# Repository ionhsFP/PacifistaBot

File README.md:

# PacifistaBot: Kit Humanoide de iniciación

Este Kit está pensado para todo aquel que quiera iniciarse en la competición de humanoides. Está diseñado con piezas estandarizadas, baratas, fácil de conseguir y pensado para ser de fácil montaje y programación. Está creado en su totalidad a base de impresión 3D, se programa desde un Arduino Nano y usa una placa controladora fácil de soldar.

Hay que destacar que el robot ha sido diseñado por OPRobots y han liberado las fuentes para que cualquiera pueda replicarlo, modificarlo o seguir desarrollándolo. Aunque su diseño inicial esté inspirado en los robots Pacifistas de la serie One Piece, el diseño es totalmente personalizable ya que tanto las manos y la cabeza, como los detalles decorativos de su pecho y piernas son totalmente modificables e intercambiables para conseguir un robot único.

Mediante este Kit se puede profundizar diferentes niveles de competencias técnicas, de las siguientes áreas STEM:

- Electrónica
- Mecatrónica
- Programación
- Dibujo
- Impresión 3D

El robot pacifistabot originalmente se ha diseñado para controlado por bluetooth. Partiendo de la idea original se ha modificado creando una nueva versión en la que se puede elegir controlarlo mediante bluetooth o mediante wifi (los 2 a la vez no se puede). En la siguiente tabla se puede ver la documentación de cada versión de robot.

| Pacifistabot                                              | Pacifistabot-ESP                                           | Pacifistabot-AlhII                                        |
| --------------------------------------------------------- | ---------------------------------------------------------- | --------------------------------------------------------- |
| [Material y Equipos](./montaje/MATERIAL-EQUIPOS.md)       | [Material y Equipos](./montaje/MATERIAL-EQUIPOS-ESPyBT.md) | [Material y Equipos](./montaje/MATERIAL-EQUIPOS-AlhII.md) |
| [Montaje y Calibración](./montaje/MONTAJE-CALIBRACION.md) | Montaje y Calibración                                      | Montaje y Calibración                                     |

El coste del material de montaje es inferior a 100 euros y para facilitar poder empezar a montar se ha documentado un listado de Material y Equipos necesarios. Clasificándolos por piezas 3D, componentes mecánicos, componentes electrónicos y equipos de trajo y herramientas.

Para guiar en el proceso de creación de robot, se ha documentado el proceso de Montaje y Calibración. En él se encuentra el proceso de montaje-ajustes mecánicos, montaje electrónico y calibración del robot.

Las especificaciones principales son:

DIMENSIONES

------

- Producto contraido: 320 x 220 x 160 mm
- Producto extendido: 450 x 600 x110 mm

PESO

------

- Producto: 1000 g ~

MATERIALES

------

- Piezas impresas en PLA o ABS
- Tornillos de acero inox.

COMPONENTES ELECTRÓNICOS

------

- 12 Servomotores MG 996R
- Bateria LiFe 6,6V 1100	mAh
- Controladora Arduino Nano
- Módulo Bluetooth hc-05
- Módulo Wifi ESP-01 (solo en Versión Pacifistabot-ESP)

COMUNICACIÓN

------

- Cable mini-Usb
- Bluetooth
- Wifi (solo en Versión Pacifistabot-ESP)
- Programación mediante OTA (Over The Air)(solo en Versión Pacifistabot-ESP)

SOFTWARE

------

- Programación: [Arduino IDE](https://www.arduino.cc/)
- Diseño electrónico: [Kicad](https://www.kicad-pcb.org/)
- Diseño mecánico: [Skeetup](https://www.sketchup.com/)
- Comunicacción: [Putty](https://www.putty.org) / [Arduino IDE](https://www.arduino.cc/) / [ScriptCommunicator](https://github.com/szieke/ScriptCommunicator_serial-terminal) /...
- APP android: [Bluetooth Electronics](https://www.keuwl.com/apps/bluetoothelectronics/) / [BlueTerm](https://play.google.com/store/apps/details?id=es.pymasde.blueterm&hl=en_US) / ...

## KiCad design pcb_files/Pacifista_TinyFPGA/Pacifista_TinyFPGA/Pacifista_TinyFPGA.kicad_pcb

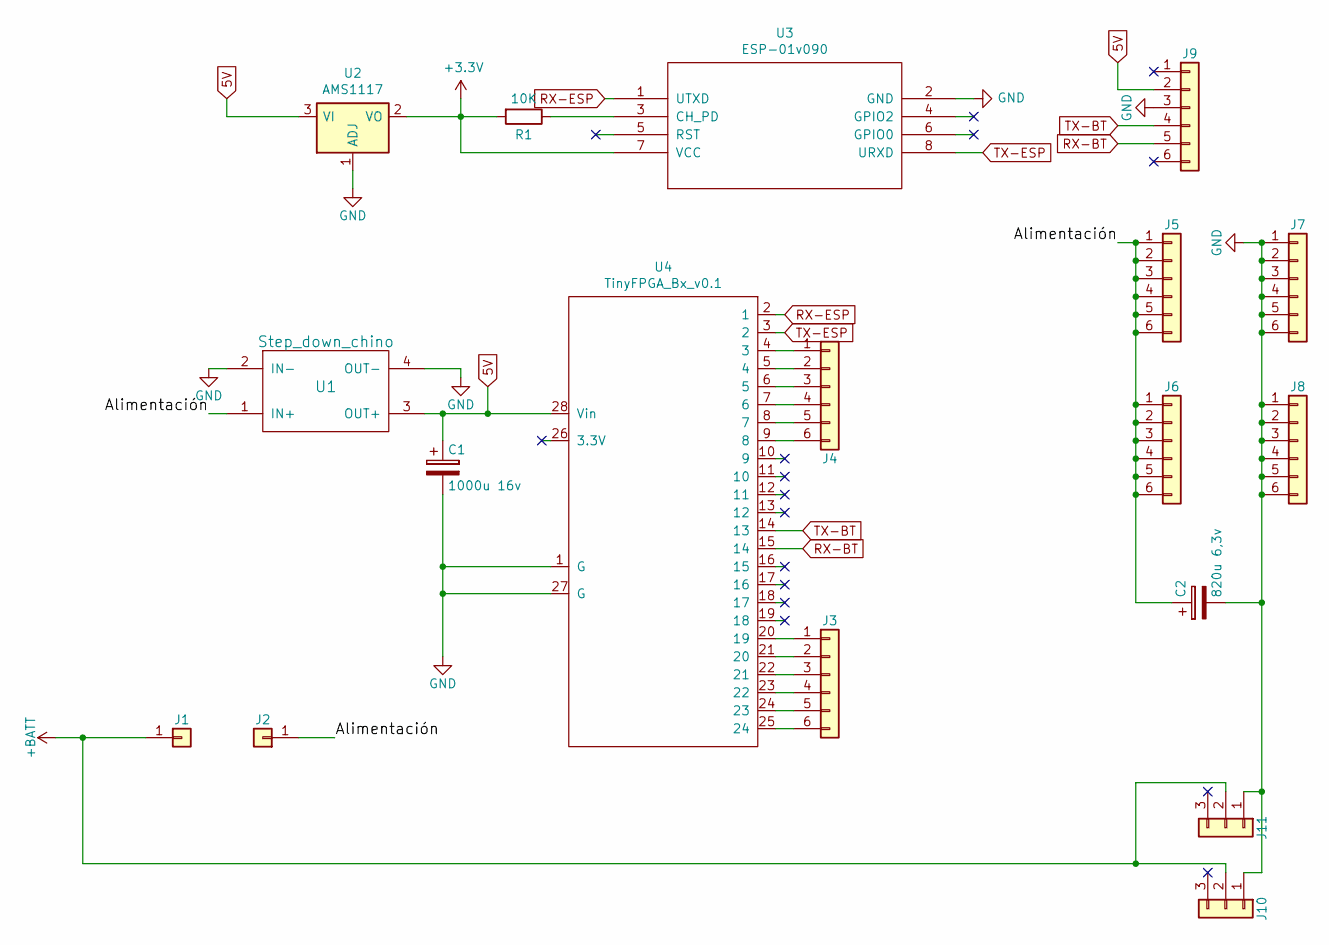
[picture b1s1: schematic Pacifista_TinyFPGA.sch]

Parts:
C1: 1000u 16v; CP_Radial_D8.0mm_P3.80mm
C2: 820u 6,3v; CP_Radial_D10.0mm_P5.00mm
J1, J2: Conn_01x01; SolderWirePad_single_1-5mmDrill
J3: Conn_01x06; PinSocket_1x06_P2.54mm_Vertical
J4, J5, J6, J7, J8: Conn_01x06; Pin_Header_Straight_1x06_Pitch2.54mm
J9: Bluetooth hc_05; Pin_Header_Straight_1x06_Pitch2.54mm
J10, J11: Conn_01x03; Pin_Header_Straight_1x03_Pitch2.54mm
R1: 10K; R_1206_3216Metric_Pad1.42x1.75mm_HandSolder
U1: Step_down_chino
U2: AMS1117; SOT-223-3_TabPin2
U3: ESP-01v090; PinHeader_2x04_P2.54mm_Vertical
U4: TinyFPGA_Bx_v0.1

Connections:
5V: C1.1, J9.2, U1.3 (OUT+), U2.3 (VI), U4.28 (Vin)
+3V3: R1.2, U2.2 (VO), U3.7 (VCC)
+BATT: J1.1, J10.2, J11.2
/Alimentación: C2.1, J2.1, J5.1, J5.2, J5.3, J5.4, J5.5, J5.6, J6.1, J6.2, J6.3, J6.4, J6.5, J6.6, U1.1 (IN+)
GND: C1.2, C2.2, J7.1, J7.2, J7.3, J7.4, J7.5, J7.6, J8.1, J8.2, J8.3, J8.4, J8.5, J8.6, J9.3, J10.1, J11.1, U1.2 (IN-), U1.4 (OUT-), U2.1 (ADJ), U3.2 (GND), U4.1 (G), U4.27 (G)
unnamed: J3.1, U4.20 (19)
unnamed: J3.2, U4.21 (20)
unnamed: J3.3, U4.22 (21)
unnamed: J3.4, U4.23 (22)
unnamed: J3.5, U4.24 (23)
unnamed: J3.6, U4.25 (24)
unnamed: J4.1, U4.4 (3)
unnamed: J4.2, U4.5 (4)
unnamed: J4.3, U4.6 (5)
unnamed: J4.4, U4.7 (6)
unnamed: J4.5, U4.8 (7)
unnamed: J4.6, U4.9 (8)
unnamed: R1.1, U3.3 (CH_PD)
RX-BT: J9.5, U4.15 (14)
RX-ESP: U3.1 (UTXD), U4.2 (1)
TX-BT: J9.4, U4.14 (13)
TX-ESP: U3.8 (URXD), U4.3 (2)

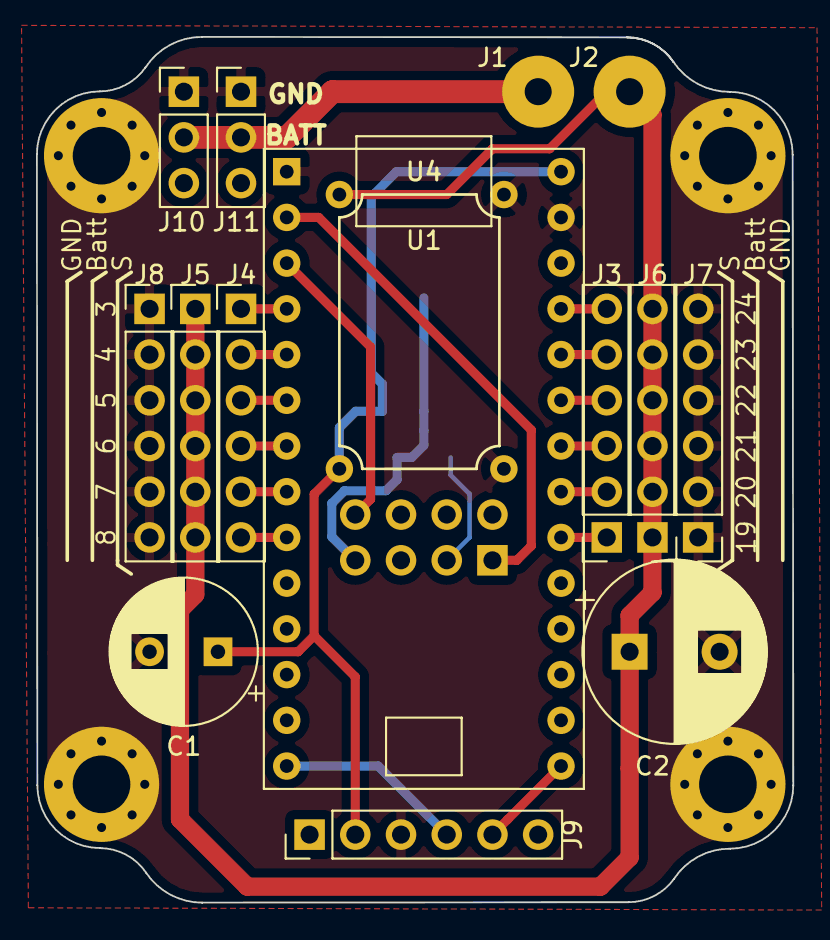
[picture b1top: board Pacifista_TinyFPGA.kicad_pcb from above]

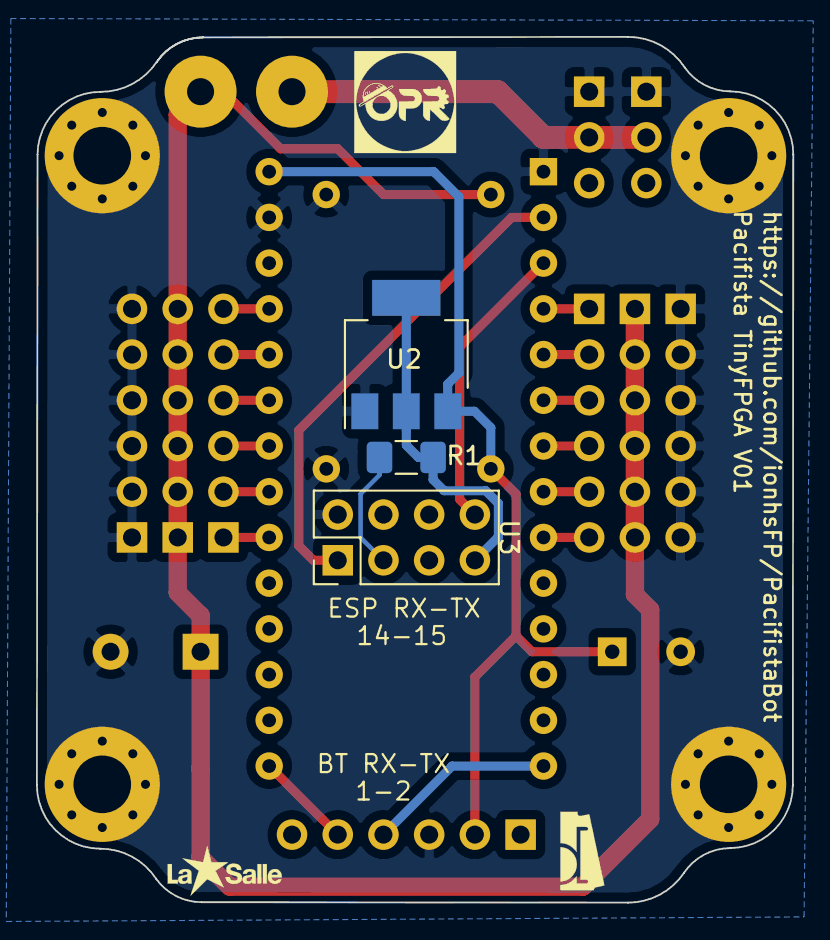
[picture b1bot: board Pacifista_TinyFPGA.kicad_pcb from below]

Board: 2 copper layers, 42.0 x 48.1 mm, 18 parts (3 on the bottom side), 22 nets.

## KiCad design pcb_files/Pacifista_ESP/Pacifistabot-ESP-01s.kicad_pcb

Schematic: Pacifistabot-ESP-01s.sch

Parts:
A1: Arduino_Nano; arduino_nano
C1: 1000u 16v; CP_Radial_D8.0mm_P3.80mm
C2: 820u 6,3v; CP_Radial_D10.0mm_P5.00mm
C3: 330nF1; C_1206_3216Metric_Pad1.42x1.75mm_HandSolder
J1, J2: Conn_01x01; SolderWirePad_single_1-5mmDrill
J3: Conn_01x09; PinHeader_1x09_P2.54mm_Vertical
J4, J5, J6, J7, J8: Conn_01x06; Pin_Header_Straight_1x06_Pitch2.54mm
J9: Conn_01x06; PinSocket_1x06_P2.54mm_Vertical
J10, J11: Conn_01x03; Pin_Header_Straight_1x03_Pitch2.54mm
R1, R6, R7: 10K; R_1206_3216Metric_Pad1.42x1.75mm_HandSolder
R2, R4: 10K; R_Axial_DIN0207_L6.3mm_D2.5mm_P7.62mm_Horizontal
R3, R5: 20K; R_Axial_DIN0207_L6.3mm_D2.5mm_P7.62mm_Horizontal
U1: Step_down_chino
U2: AMS1117; SOT-223-3_TabPin2
U3: ESP-01v090; PinHeader_2x04_P2.54mm_Vertical

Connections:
5V: A1.27 (5V), C1.1, J9.2, R7.2, U1.3 (OUT+), U2.3
+3V3: R1.2, U2.2, U3.7 (VCC)
+BATT: J1.1, J10.2, J11.2
/Alimentación: C2.1, J2.1, J5.1, J5.2, J5.3, J5.4, J5.5, J5.6, J6.1, J6.2, J6.3, J6.4, J6.5, J6.6, R4.1, U1.1 (IN+)
GND: A1.4 (GND), A1.29 (GND), C1.2, C2.2, J7.1, J7.2, J7.3, J7.4, J7.5, J7.6, J8.1, J8.2, J8.3, J8.4, J8.5, J8.6, J9.3, J10.1, J11.1, R3.2, R5.2, R6.2, U1.2 (IN-), U1.4 (OUT-), U2.1, U3.2 (GND)
unnamed: A1.2 (D0/TX), R2.1
unnamed: A1.7 (D4), J3.1
unnamed: A1.8 (D5), J3.2
unnamed: A1.9 (D6), J3.3
unnamed: A1.10 (D7), J3.4
unnamed: A1.11 (D8), J3.5
unnamed: A1.12 (D9), J3.6
unnamed: A1.13 (D10), J3.7
unnamed: A1.14 (D11), J3.8
unnamed: A1.15 (D12), J3.9
unnamed: A1.19 (AD0/D14), J4.1
unnamed: A1.20 (AD1/D15), J4.2
unnamed: A1.21 (AD2/D16), J4.3
unnamed: A1.22 (AD3/D17), J4.4
unnamed: A1.23 (AD4/D18), J4.5
unnamed: A1.24 (AD5/D19), J4.6
unnamed: A1.26 (AD7), R4.2, R5.1
unnamed: C3.1, J9.6
unnamed: R1.1, U3.3 (CH_PD)
RST: A1.3 (RESET), C3.2, R6.1, R7.1
RX: A1.1 (D1/RX), J9.5, U3.1 (UTXD)
TX: J9.4, R2.2, R3.1, U3.8 (URXD)

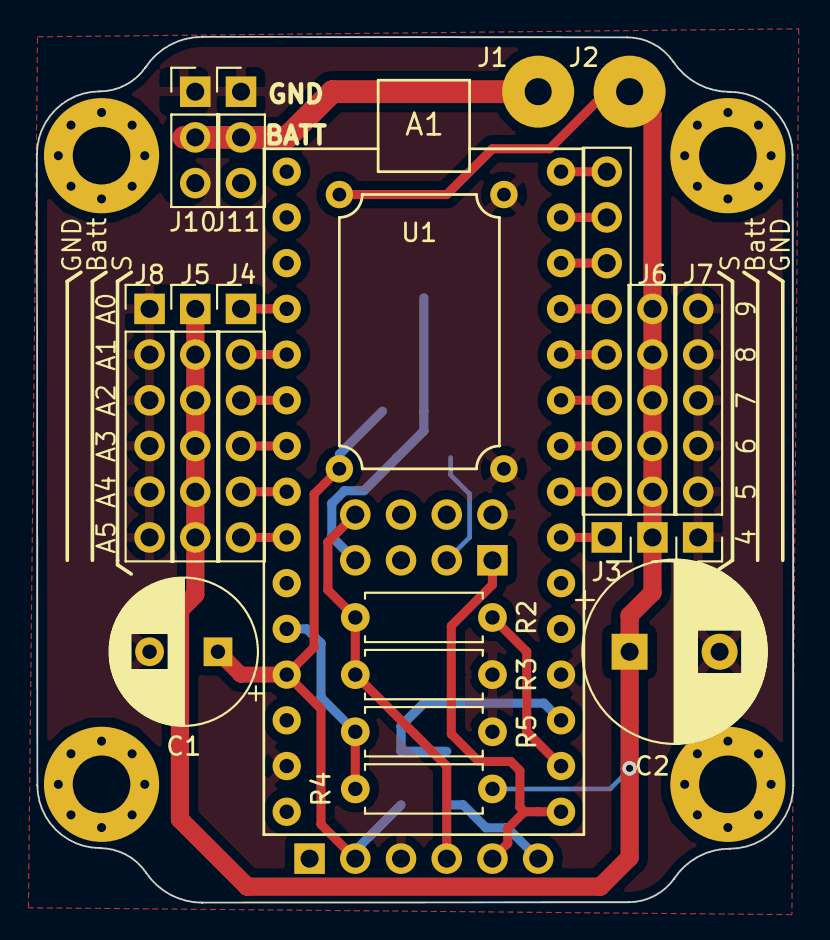
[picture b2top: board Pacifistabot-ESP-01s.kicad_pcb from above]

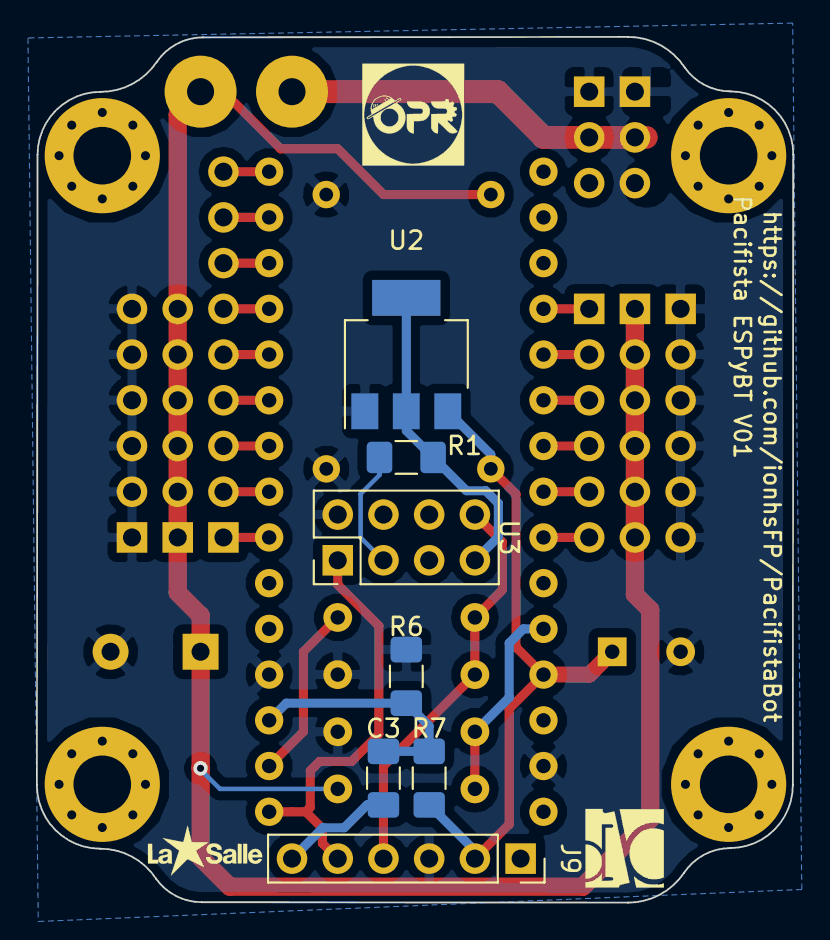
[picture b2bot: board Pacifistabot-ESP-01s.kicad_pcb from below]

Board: 2 copper layers, 42.0 x 48.1 mm, 25 parts (7 on the bottom side), 27 nets.

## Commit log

2019-04-15 Subida de archivos masivo
2019-12-03 Documentación sobre le montaje
2019-12-03 Actualización del Readme
2019-12-05 Actualización bug link
2020-01-07 Creacion de lista de materiales para la pcb ESP-BT
2020-01-14 Actualizacion documentacion a version Pacifistabot-ESP
2020-01-22 actualización componentes 3D
2020-01-31 correccion bugs de la documentacion
2020-01-31 correccion bug link video
2020-01-31 correccion bug
2020-01-31 correccion
2020-05-15 Corrección de los pines de la PCB y el logo de DB
2020-06-17 Creación de alhambra
2020-06-26 Creación de lista de materiales de la PCB AlhambraII
2020-06-26 corrección link
2020-06-26 Actualización de los links de la pcb AlhII
2020-06-26 Actualizar fallos con links
2020-06-26 Corrección fallo de pieza 14 stl
2020-06-26 Subida de los archivos gerbers
2020-08-31 Subida del pcb freecad tinyfpga
